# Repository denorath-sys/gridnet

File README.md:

# GRIDNET — Powerline Mesh Terminal

> *Communicate over the power grid. No internet. No GSM. No servers.*

---

## What Is GRIDNET?

GRIDNET is an open hardware mesh communication terminal that uses **existing power line infrastructure** as its transmission medium. Plug the adapter into any wall outlet — the terminal connects to your neighborhood network instantly.

No internet required. No cell towers. No central servers. No accounts.

When grid power fails, the adapter runs from the Terminal's battery over a cable you plug in — the wire is still a conductor whether or not it's energised, so the network keeps working.

The Wi-Fi mesh is not a fallback for the powerline. The two carry to different places: PLC reaches **electrical** neighbours (the same distribution segment, and in practice the same phase), the mesh reaches **physical** ones (adjacent flats, through walls). A neighbour on another phase in the same building is often unreachable over the wire and one mesh hop away. Both run all the time and the router picks per destination — see [`docs/channels.md`](docs/channels.md).

```
Tether:      [Terminal] ←WiFi→ [its own PLC Adapter]      private link to your own modem
PLC:         [Adapter] ←powerline→ [Adapter]              same segment, same phase
Mesh:        [Adapter] ←ESP-NOW→ [Adapter]                physically adjacent, any phase
Outage mode: Grid is down — plug the Terminal into the adapter, network stays alive on battery
```

---

## Why Does This Exist?

Every year, earthquakes, floods, and infrastructure failures cut millions of people off from communication. The internet fails. Cell towers fail. But in most of these scenarios, one thing survives: **the physical power line wiring**.

GRIDNET turns that infrastructure into a resilient local network — inspired by Minitel (France's pre-web national terminal network), FidoNet (a global decentralized BBS built by hobbyists), and the ThinkPad design philosophy (tools built to last).

---

## Hardware Overview

The system consists of two units:

### Terminal
The user-facing device. ThinkPad-inspired clamshell form factor.

| Component | Details |
|---|---|
| **Processor** | GD32VF103CCT6 — RISC-V, 108MHz, 32KB RAM, 256KB Flash |
| **Wireless** | ESP32-C3-MINI-1U — Wi-Fi 2.4GHz mesh + Bluetooth 5.0 LE |
| **Display** | 5.0" TFT LCD, 800×480, RA8875 controller (onboard SDRAM frame buffer), 256 colors, amber-tinted backlight |
| **Keyboard** | 40-key mechanical (Kailh LP), amber LED backlight, red TrackPoint |
| **Right panel** | M1–M4 macro keys + 4×4 numeric keypad + speaker |
| **Speaker** | 1W / 8Ω + PAM8403 amplifier |
| **Storage** | 8MB SPI Flash (LittleFS) + microSD slot |
| **Battery** | 2× 18650, 3350mAh-class genuine cells (~6700mAh total), ~17h active use (screen on) / ~17.5 days standby (screen off, mesh-listen only) — see [`docs/firmware-arch.md`](docs/firmware-arch.md) Power Budget for the full breakdown |
| **Charging** | USB-C, ~4 hours |
| **Antenna** | External, ≤2.33 dBi, on a bulkhead SMA in the case wall — reached by an MHF III / W.FL pigtail from the module's own antenna jack, not by board copper (the module has no RF pad; see [`hardware/pcb/main-board`](hardware/pcb/main-board)) |
| **Dimensions** | 260 × 160 × 28mm, ~680g |
| **OS** | Zephyr RTOS, custom RISC-V BSP |

### PLC Adapter
Separate unit. Plugs directly into any wall outlet (Schuko). Connects to terminal over Wi-Fi — no cables in normal use; during a grid outage the user plugs a USB-C cable in to power it from the Terminal's battery. Replaceable independently.

| Component | Details |
|---|---|
| **PLC SoC** | ST7580 — CENELEC EN50065, OFDM/FSK (band selection under review, see [`docs/electrical-safety.md`](docs/electrical-safety.md)) |
| **Wireless** | ESP32-C3 — Wi-Fi AP for terminal connection |
| **Outage power** | USB-C inlet from the Terminal's battery + 1F supercapacitor hold-up |
| **PLC supply** | MT3608 boost, 5V → 12V for the ST7580's power amplifier |
| **Protection** | TVS P6KE250CA + MOV S20K275 (2 layers; the relay/optocoupler layer went with the inverter) |
| **Power** | HLK-5M05 SMPS, 230VAC → 5VDC |
| **Indicators** | 3× LED: Power / PLC / Wi-Fi |

**Prototype BOM cost: ~$150.22 USD** for one Terminal plus one Adapter — ~$104.35 and ~$45.87 respectively (single unit, retail component pricing). See [`hardware/bom.md`](hardware/bom.md) REV 0.10 for the full breakdown, including why the earlier ~$112 and ~$166.65 figures were both wrong.

---

## Architecture

### Communication Stack

```
┌─────────────────────────────────────────┐
│           APPLICATION LAYER             │
│   Messaging / Games / Forth Apps        │
├─────────────────────────────────────────┤
│           ROUTING LAYER                 │
│   Store-and-forward, 7-day retention    │
│   Mesh routing, automatic repeating     │
├─────────────────────────────────────────┤
│           CHANNEL LAYER                 │
│   Two interfaces, chosen per            │
│   destination by cost — not ranked      │
├─────────────────────────────────────────┤
│           PHYSICAL LAYER                │
│   ST7580 OFDM/FSK, EN 50065-1 limited   │
│   ESP32-C3 Wi-Fi 2.4GHz                 │
└─────────────────────────────────────────┘
```

### Packet Format

```
[AA AA AA][55][LEN 2B][SRC 4B][DST 4B][SEQ 4B][TYPE 1B][PAYLOAD][CRC16 2B]
 preamble  sync  len    source   dest    seq     type     data      checksum

TYPE byte:  [7] SIGNED   [6] RELAYED   [5:0] type code
```

### Addressing

Hierarchical 4-byte address — no central registry required:

```
[CITY 1B][DISTRICT 1B][BUILDING 1B][UNIT 1B]
  01         03           07          12       →  01.03.07.12
```

### Outage Operation

The wire is a conductor whether or not the grid is energising it, so PLC
signalling works during an outage. What stops is the adapter's own power:
it runs from mains, and there is no battery inside it.

So during an outage the adapter runs from the Terminal's battery over a
USB-C cable the user connects. A supercapacitor in the adapter holds it up
long enough to tell the Terminal that mains has gone, so the Terminal can
prompt for the cable. Roughly 5–6 hours of operation with the screen on,
~9 hours with it off.

Nothing is injected onto the wire, and there is no arbitration between
adapters — every node transmits normally under CSMA/CA, exactly as it does
when the grid is up.

Earlier revisions specified a 24V "inverter mode" here instead. It was
removed: it could never have run (the adapter had no power source during
an outage) and it sat 5–24× outside EN 50065-1's signal limits. See
[`docs/plc-adapter-power.md`](docs/plc-adapter-power.md) for the full
analysis, and [`docs/electrical-safety.md`](docs/electrical-safety.md) for
the compliance correction.

### Software Architecture

- **RTOS:** Zephyr (RISC-V support, tickless idle, LittleFS)
- **Boot time:** < 500ms target
- **Tasks:** CHANNEL_MONITOR (0) → PLC_RX (1) → MESH_RX (2) → ROUTER (3) → KEYBOARD (4) → UI (5) → BACKGROUND (6)
- **Filesystem:** LittleFS on 8MB Flash + microSD

Boot screen (Commodore 64 homage):
```
**** GRIDNET OS V1.0 ****
64K RAM SYSTEM  8192K FLASH  BLUETOOTH 5.0
PLC CHANNEL: ACTIVE [3 NODES FOUND]
WIFI BRIDGE: STANDBY  MICROSD: 32GB

READY.
█
```

### Forth VM — Application Platform

Users write and share applications in a sandboxed Forth interpreter (~2KB RAM). Apps are distributed peer-to-peer over the network — like the BBS era.

Security constraints: source address lock, rate limit (5 packets/sec), max 256 bytes/message, filesystem isolation per app.

Example — local market order system in ~15 lines (verified against the
reference VM in [`tools/forth-vm`](tools/forth-vm) — see that directory's
README for why `S"` and `KEY? IF KEY ...` are used instead of the shorter
but non-functional `"` / `KEY? SEND-MSG` you might expect):
```forth
: HEADER
  0 0 S" ╔═══════════════╗" WRITE
  0 1 S" ║  CORNER SHOP  ║" WRITE
  0 2 S" ╚═══════════════╝" WRITE ;

: ORDER
  HEADER
  0 4 S" 1. Bread  2. Milk" WRITE
  KEY? IF KEY S" 01.03.07.99" SEND-MSG THEN ;

: MAIN BEGIN ORDER 1000 WAIT AGAIN ;
MAIN
```

---

## Electrical Safety

GRIDNET puts a low-voltage signal on the mains through a transformer. It does not energise the wire.

- **Signal level is bounded by EN 50065-1**: 5 Vrms at 9 kHz falling to 1 Vrms at 95 kHz. The ST7580's power amplifier delivers 14 V p-p (4.95 Vrms) — ST sized the part to land on that limit — and the adapter adds a hardware current limit as a backstop.
- **PLC signals sit at 95–148.5 kHz**, roughly 2000–3000× the grid frequency. Every household power supply filters that band out; the signal is invisible to their power circuits. Same principle as HomePlug and smart metering, deployed in millions of homes for two decades.
- **Galvanic isolation is mandatory and load-bearing.** The ST7580 reaches the line only through the coupling transformer, and the HLK-5M05 is an isolated supply. The USB-C cable to the Terminal sits on that isolated secondary — the user handles it while the adapter is in a wall socket, so this barrier is what stands between them and the mains.
- **Two protection layers**: TVS (P6KE250CA) for transients, MOV (S20K275) for sustained overvoltage.

⚠️ **One open compliance item**: no EN 50065-1 conformance claim is justified until a conducted-emission sweep is run on a prototype. The band allocation itself is settled — the A-band (9–95 kHz) is reserved for electricity suppliers, so GRIDNET uses B (95–125 kHz) and C (125–140 kHz), and the hardware commits to that choice through Board 1's coupling network ([`docs/plc-coupling.md`](docs/plc-coupling.md), [`docs/protocol.md`](docs/protocol.md)). What remains is the measurement, which needs hardware that does not exist yet. See [`docs/electrical-safety.md`](docs/electrical-safety.md) REV 0.6, which also corrects an earlier claim in this project that a 24V injection was within EN 50065 limits. It was not.

---

## Use Cases

| Scenario | Description |
|---|---|
| 🏚 Disaster response | Coordinate with neighbors when grid, internet, and cell are all down |
| 🏘 Neighborhood messaging | Hyperlocal communication without internet subscriptions |
| 🛒 Local commerce | Shops write their own order systems in Forth — no cloud, no monthly fee |
| 🎮 Games | Turn-based strategy and text adventures played over the power grid |
| 🔒 No cloud | No accounts, no logs, no servers — nothing leaves the neighbourhood. Note that this is *not* the same as confidentiality: the protocol has no encryption yet, and store-and-forward means a message can sit in a relaying neighbour's device for up to 7 days in plaintext. See "Known Gaps" below |
| 👾 Retro / Hacker | Amber display, mechanical keyboard, Forth VM, RISC-V. It boots to READY. |

---

## Project Status

| Component | Status |
|---|---|
| Hardware architecture (dual-board design) | ✅ Complete |
| Communication protocol stack | 🔄 **Under revision — was marked complete, and wasn't.** Three separate design faults are now documented: it does not scale ([`docs/routing.md`](docs/routing.md) — twenty nodes on one segment spend 30.7% of the channel on routing advertisements), it has no authentication of any kind ([`docs/threat-model.md`](docs/threat-model.md)), and its channel model ranks the Wi-Fi mesh as a fallback for the powerline when the two reach different sets of nodes ([`docs/channels.md`](docs/channels.md)). Each has a decided design; none is implemented, and [`docs/protocol.md`](docs/protocol.md) still specifies the old behaviour alongside notices of what replaces it |
| PLC Adapter power architecture ([`docs/plc-adapter-power.md`](docs/plc-adapter-power.md)) | ✅ Complete — adapter runs off the Terminal's battery during an outage; the 24V inverter and its master-election protocol were removed (never able to run, and outside EN 50065-1) |
| Protection circuit (TVS + MOV) | ✅ Complete — two layers, not three: the relay/optocoupler layer went with the inverter. Parts selected ([`hardware/bom.md`](hardware/bom.md)) and now drawn — `P6KE250CA` and `S20K275` are in Board 1's schematic and placed on its PCB |
| Main Board schematic + PCB layout ([`hardware/pcb/main-board`](hardware/pcb/main-board)) | ✅ Complete — custom parts datasheet-verified, PCB placed, routed, ground-poured on both layers, DRC clean (0 violations, 0 unconnected). REV 0.7 was a pre-fab design review that caught a refdes-drift bug placing parts in each other's positions (crystal load caps 51mm from the crystal), a boost-converter switching loop spread across 63mm, and every trace at 0.2mm including a 2.4A path. REV 0.8 found the antenna path was fiction — a phantom U.FL duplicating the module's own jack, a trace nothing could drive, and an invented `ANT` symbol pin — and that the "grid of stitching vias" was nine vias in one column, because `BOX2I.Inflate()` mutates in place (now 167, worst-case return path 55mm → 16.8mm) — see that directory's README |
| PLC/Power Board (BOM's Board 1, the PLC Adapter's PCB — see [`hardware/pcb/plc-board`](hardware/pcb/plc-board)) | ✅ REV 0.3 schematic complete, ERC-clean (350 warnings, 0 errors). Power architecture: Terminal USB-C inlet, Schottky ORing, supercapacitor hold-up, 5V→12V boost feeding the ST7580's `VCC`, hardware transmit-current limit. Line coupling now built too — transmit active filter around the ST7580's own PA, receive resonant filter, and the coupling transformer into the mains. Topology from ST's AN4068, values rescaled from its A-band reference design to GRIDNET's 95–140 kHz band ([`docs/plc-coupling.md`](docs/plc-coupling.md)). PCB placement complete (REV 0.5), now a **four-layer** board: L1/L4 signals, In1.Cu GND plane, In2.Cu +5V plane. Four layers because the ST7580's nine +5V pads on a 48-pin 0.5mm-pitch package need a plane, and two two-layer copper layers are already spoken for by ground and the mains barrier — see that directory's README for the four runs that established it. The 7.96mm isolation barrier cuts all four layers and only the AC-DC module and the coupling transformer cross it; verified geometrically on every pad, track, via and filled zone. **Routed (REV 0.7)**: DRC 0 errors, 0 unconnected, isolation barrier clean on copper. REV 0.6's "one connection short" turned out to be the first gap the repair loop could not close, not the last — the boards behind it had up to nine, all on the ST7580's 0.5mm-pitch QFN. Closing them took a fanout that stopped walling in the signal pins, two parts moved off the QFN's pin field, a 0.15mm escape rule around that one package only (the rest of the board stays 0.2mm), and a repair router that routes through other copper and lifts only what it crosses. The ST7580's grounding was then checked against its datasheet: its VCC capacitor now returns to VSS (Figure 8) rather than through the VSS–GND ferrite, and its exposed pad's thermal vias land on a VSSA island under it. DRC 0 warnings. Still wants a human look at the analog copper around the ST7580 before fab. |
| Case design (CAD) | 📋 Planned — only target external dimensions exist (see Hardware Overview); no CAD model |
| Software architecture (Zephyr + Forth VM) | ⚠️ Complete on paper, with one known conflict — [`docs/threat-model.md`](docs/threat-model.md) found that Ed25519's 1–2KB working set does not fit the `ROUTER` task's 2048B stack, which is why the crypto moves to the ESP32-C3 and the node's identity ends up belonging to that module |
| Electrical safety analysis | ✅ Complete |
| Protocol & Forth VM reference prototypes ([`tools/`](tools/), Python, pre-hardware validation) | ✅ Complete — 90 tests pass. Note that `protocol-sim` implements the protocol as specified today, so the routing, authentication and channel revisions above will need to land there too before they mean anything |
| **PCB fabrication / Hardware prototype** | 🔄 Next step — Main Board has been through two design-review passes and is DRC-clean. RF layout is no longer on its list: there is no RF net on the board (the antenna is a cable assembly from the module's own jack). The stackup is no longer an open decision — it is now `STACKUP` in `build_pcb.py` (1.6mm FR-4, two layers, 1oz copper) and written into the board's own design rules, which turned up that KiCad's manufacturing minimums had been left at zero all along: every "0 violations" this project reported before that had been measured against no process limit at all. The board passes the real rules unchanged. What is left before fab is a return-path review of the SPI/I2C buses and a human eye on the autorouted copper (see [`hardware/pcb/main-board`](hardware/pcb/main-board) "What's not done yet"). Board 1 is placed, four-layer and routed (REV 0.7, DRC-clean). Before it is fabricated it needs a human review of the autorouted analog copper, a part for the ST7580's VSS–GND ferrite (FB1, ≥1.5A), and the mains creepage figure confirmed against the standard; before any EN 50065-1 claim it needs a conducted-emission sweep |
| Embedded firmware (Zephyr, on real hardware) | 📋 Planned — starts after PCB prototype |
| **Link-budget survey** (rides along with the prototype) | 📋 Blocking four documented decisions — cross-phase attenuation, how much of a real segment hears itself, mesh reach through actual walls, and ESP-NOW throughput for small frames. Every routing and channel figure in this project is arithmetic from datasheet-class assumptions, not evidence. This is now the cheapest thing that would tell us whether the design is right |
| Field testing | 📋 Planned |

---

## Known Gaps

Things this design does not currently do. They are listed here rather than
left for a reader to discover, because two of them affect whether the
network can be trusted in the situation it exists for.

**There is no message authentication.** `SRC` is a plaintext field in the
packet header, and on a shared broadcast medium any node can set it to any
value. The sandbox rule in [`docs/protocol.md`](docs/protocol.md) —
"source address locked, app cannot spoof sender" — constrains a Forth app
running on its own device; it says nothing about a modified node. The
consequences follow directly:

- **ROUTE poisoning.** The routing layer is distance-vector with no
  authentication, so any node can advertise `hop_count 0` for an address it
  does not own and pull that traffic to itself.
- **Forged emergency broadcasts.** `BROADCAST 0x03` is flooded to the whole
  mesh and signed by nothing.
- **Storage exhaustion.** Store-and-forward holds messages for 7 days on
  behalf of unauthenticated senders.
- **Unverified code distribution.** `APP_DATA 0x10` moves Forth applications
  peer-to-peer, from peers whose identity is not established.

Firmware updates *are* signed — Ed25519, verified by the bootloader
([`docs/firmware-arch.md`](docs/firmware-arch.md)). The network layer has
no equivalent.

A threat model now exists for closing this: [`docs/threat-model.md`](docs/threat-model.md)
scopes the adversary as a hostile neighbour on the same wire, and records
the decisions — Ed25519 identity bound to an address by trust-on-first-use,
signing tiered so that routing, broadcasts and code are always signed while
ordinary messages are opt-in, and the crypto moved to the ESP32-C3 because
Ed25519's working set does not fit the `ROUTER` task's 2KB stack. **Nothing
is implemented**; the wire format above is still the unauthenticated one.

It is also explicit about what authentication does *not* fix — a signed
route advertisement proves who said it, not that the route exists — and
about what stays out of scope: device theft, traffic analysis and jamming.

**`ROUTE` does not scale, independently of security.** Twenty nodes on one
distribution segment would spend 30.7% of a 2.4 kbps channel on routing
advertisements alone. [`docs/routing.md`](docs/routing.md) redesigns it
around a property the original missed — a PLC segment is a broadcast domain,
so one-hop neighbours can be learned passively at zero airtime cost — which
takes the same case to 1.89%. That document also states, for the first time
in this project, what topology the network is assumed to have, and flags
that the assumption has never been measured.

**Duplicate addresses are not detected.** Addresses are self-assigned with
no registry, and `docs/protocol.md` currently attributes collision
detection to CSMA/CA. That is a media-access mechanism — it detects a busy
channel, not two nodes claiming `01.03.07.12`. Nothing in the protocol
notices the duplicate, and the routing table oscillates when it happens.

**No encryption.** Message contents are plaintext on the wire and plaintext
in every relaying device's store-and-forward queue.

---

## Repository Structure

```
gridnet/
├── README.md
├── LICENSE                    (CERN-OHL-W-2.0)
├── CONTRIBUTING.md
├── hardware/
│   ├── pcb/
│   │   ├── main-board/         (Board 2 — KiCad schematic + routed, ground-poured PCB, see its README)
│   │   └── plc-board/          (Board 1 — KiCad schematic + routed PCB, see its README)
│   └── bom.md                 (bill of materials)
├── docs/
│   ├── protocol.md            (full protocol stack)
│   ├── firmware-arch.md       (Zephyr + Forth VM)
│   ├── threat-model.md        (adversary scope, attacks, auth decisions)
│   ├── routing.md             (why ROUTE doesn't scale, and the redesign)
│   ├── channels.md            (PLC vs mesh: what each actually reaches)
│   ├── electrical-safety.md   (CENELEC compliance)
│   ├── plc-adapter-power.md   (adapter power architecture + EN 50065 analysis)
│   └── plc-coupling.md        (line coupling network: AN4068 retuned for B+C)
├── firmware/
│   └── README.md              (planned structure — embedded firmware not started)
├── tools/
│   ├── protocol-sim/          (Python reference implementation of docs/protocol.md)
│   └── forth-vm/              (Python prototype of the sandboxed Forth VM)
└── media/
    ├── logo-cyan.svg
    └── logo-silver.svg
```

Note: `hardware/case/` and `hardware/schematics/` (now just a pointer to
`hardware/pcb/`) aren't in the tree above because there's nothing under
either yet worth listing — see the Project Status table above.

---

## Looking For

- Hardware engineer with embedded systems / PCB experience
- Anyone with real-world ST7580 / PLC field experience
- Zephyr RTOS developers (RISC-V BSP, driver development)
- Forth enthusiasts — help design the VM standard library
- Beta testers willing to run a node in their building

Open an Issue or email directly if you're interested in collaborating.

---

## Inspiration

**Minitel** — France's pre-web national terminal network. A whole country connected, locally, before the internet existed.

**FidoNet** — A global decentralized BBS network built by hobbyists. Store-and-forward over phone lines. No servers. No company.

**ThinkPad** — A design philosophy: every detail intentional, built to last, keyboard first.

---

## License

Hardware designs and documentation: [CERN Open Hardware Licence v2 — Weakly Reciprocal (CERN-OHL-W-2.0)](https://ohwr.org/cern_ohl_w_v2.txt)

Firmware (when released): GPL-3.0

© 2026 Yasar — Open Hardware Project

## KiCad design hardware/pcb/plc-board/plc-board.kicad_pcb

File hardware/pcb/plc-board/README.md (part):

GRIDNET — PLC/Power Board KiCad Schematic + PCB
REV 0.7 (Board 1, the PLC Adapter's own PCB — see "Board 1 is the PLC
Adapter's PCB" below.)

What changed in REV 0.7
------------------------

**The board is routed.** `route.sh` now runs from placement to a finished
board: 753 track segments and 173 vias over F.Cu and B.Cu, both planes
poured, DRC **0 errors, 0 warnings, 0 unconnected**, and
`check_isolation_barrier()` clean on copper.

**U4's grounding now follows the ST7580 datasheet** (DocID022644 Rev 2), read
for this pass rather than assumed:

- **C11 decouples VCC to VSS, not GND.** Figure 8 draws VCC's capacitor to
  VSS, and "all supply voltages must be properly filtered to their respective
  ground". C11 went to GND, which put the PA's supply loop — up to 1 A,
  I(PA_OUT)MAX — through FB1, the ferrite Figure 9 puts between VSS and GND.
  Every other supply capacitor already matched Figure 8.
- **The exposed pad's thermal vias land on copper.** Table 2: the pad is
  "electrically connected to VSSA" and should be "thermally connected to a
  copper ground plane"; Table 5's 50 °C/W is "mounted on a 2-side + vias PCB
  with a ground dissipating area on the bottom side". The plane under it is
  GND, so its sixteen vias were cut out of it and DRC called them dangling.
  The pour step now adds a VSSA island under the pad, inside U4's pin ring,
  on In1.Cu (37 mm²) and B.Cu (28 mm², less where escape routes cross).
- **Tying the pad to GND directly would have been wrong.** Figure 9 joins the
  exposed pad, VSSA and VSS, and reaches GND only through a ferrite bead —
  which is what the schematic already did.
- **FB1 carries the PA's DC return** (the 12V boost is GND-referenced), so
  `hardware/bom.md` now asks for ≥1.5 A and low DC resistance.

Also: `route.sh` bounds Freerouting with `FREEROUTING_TIMEOUT` (300 s) and
treats a run that writes no session as a failed attempt. The same DSN that
finished in 17 s on one run sat for ten minutes on the next, and the import
of nothing used to hand all 172 nets to the repair router.

REV 0.6 reported every run ending "one connection short". That was wrong, and
the reason it was wrong is the first thing this pass found:

**`finish_routing.py` stopped at the first pair it could not repair.** So
"one short" was the first hard gap, not the last — the board behind one such
report still had nine. The loop now sets a hard pair aside, works the rest,
retries set-aside pairs whenever the gap count falls below its best so far,
and lists every remaining gap when it gives up. Counting progress as "fewer
gaps than ever" rather than "a repair reported success" matters: one run
"finished" the same `/ST_VDD_A` gap six times with copper that never closed
it.

Once the real list was visible, every remaining gap was on **U4, the ST7580**
— a 48-pin 0.5mm-pitch QFN with its power pins interleaved among signals —
and the causes were in this toolchain and this placement, not in luck:

- **The repair rip-up looked at the wrong end.** It searched for neighbours to
  move around the pair's *second* end; on every REV 0.6 run the stranded end
  was the first (U4 pins 39 and 41).
- **The power fanout walled in the signals.** One via per power pad, in line,
  1.6mm out: each blocked both neighbouring rows, and on U4's right edge
  (48 47 +5V, 46 VDD_B, 45 GND, 44 43 42 +5V, 41 40 39 signals) every signal
  had one across its only way out. Adjacent same-net pads now share one
  bridged via from the run's middle; spacing is checked by real distance,
  stubs included; +5V goes before GND (GND has the F.Cu pour to fall back on);
  a pad boxed in on both sides can dogleg into an unused neighbour's row (U4
  pin 33, between two +5V stubs, lands its via beside NC pin 32); and a pad
  left without a fanout is reported. It used to skip three of U4's thirteen
  silently; pin 45 then came back from routing joined to nothing but a 1.8mm²
  sliver of pour.
- **R6 and C15 sat on top of U4's pin field.** R6 was 0.4mm above pins 3–8,
  leaving 1.35mm for two fanout vias and the five JTAG signals plus RESETN on
  their way to J3. C15 sat across pins 9–12, far from the Rx tank it belongs
  to (RX_IN is pin 19, on the *left* edge). R6 moved up and left of the pins;
  C15 moved beside R20 and L2.
- **0.2mm track and 0.2mm clearance cannot get U4's signals out.** Pins 4 and
  5 sit between pin 3's +5V via and pin 6's GND via, whose copper is 0.9mm
  apart; two tracks need 1.0mm. Adjacent pins cannot fan out at 45° either
  (0.354mm between them, 0.4mm needed). So there is now a **fine-pitch escape
  rule, around U4 only**: a named rule area `U4_ESCAPE` (courtyard + 3mm) and
  a custom rule in `plc-board.kicad_dru` drop clearance to 0.15mm inside it,
  and U4's signal nets form an `Escape` netclass routed at 0.15mm. Everything
  else stays at 0.2/0.2, which DRC was checked to still enforce outside the
  area. `PA_OUT` and `VSSA` stay at Default width — they carry the PA's
  current. The process minimum in `STACKUP` drops to 0.15mm so the rule is
  legal; JLCPCB's standard four-layer process goes to 0.09mm.

And the repair router learned to finish:

- **Route through, lift only what is crossed.** Re-routing every neighbour
  from scratch as a pad chain kept failing on the one neighbour that could not
  get back in. `lift_route()` instead runs A* with other nets' unlocked copper
  passable at a cost, then lifts exactly the segments the result comes within
  clearance of; the cut ends are repaired as ordinary gaps. Neighbours with
  more than six pads (`/ST_VSSA`) are cut locally rather than re-routed.
- **Orphan pads.** A planed pad on its own pour island with no via is found
  and stitched — from the pad if it can escape, else anywhere inside the
  island, lifting the one or two segments in the chosen spot's way.
- **Locked copper.** Every via and stub `build_pcb.py` places is locked, and
  repair never touches locked copper. Before this, ripping up `/ST_VSSA` as a
  neighbour removed U4's sixteen thermal vias, which nothing would have put
  back. The locks survive the Freerouting round trip.
- **The board edge.** Freerouting does not keep KiCad's 0.5mm copper-to-edge
  rule (it laid `/ST_RESETN` 0.26mm from the top edge), so offending
  autorouter copper is removed and re-routed. The repair router's own margin
  now includes the copper's half-width and is measured from the Edge.Cuts
  geometry; `GetBoardEdgesBoundingBox()` includes the outline's line width and
  sat 0.075mm outside the real edge, and on the right and bottom the margin was
  counted from the end of a grid 1mm larger than the board.
- **Zones are refilled after every repair**, since the pour now comes before
  repair, and **a cleanup pass** deletes what repair leaves behind (dangling
  stubs, duplicate vias, Freerouting's via 0.05mm off a locked fanout via),
  driven by DRC's own UUIDs, then re-checks that nothing came apart.
- **Each repair step runs in a fresh Python process.** Once copper has been
  taken off a board, KiCad 9's SWIG layer hands back any later board's objects
  as bare `SwigPyObject`s and segfaults on exit. `route.sh` can also keep each
  failed attempt's board (`KEEP_FAILED=dir`); the next attempt's placement
  used to overwrite it.

Two more corrections: `route.sh` drops the escape area from the DSN (KiCad's
Specctra exporter writes every rule area as a keepout, which would have fenced
Freerouting out of exactly that region), and rule areas are now honoured by
what they forbid rather than by being rule areas at all.

The routed board came from the first attempt of the run that produced it, but
attempts differ — Freerouting is not deterministic — and earlier runs with
only some of these changes needed several. This was produced with KiCad 9.0.3
and Freerouting 2.2.4 on Java 25; KiCad 9.0.3 reproduces the REV 0.6 placement
exactly (same parts, nets, vias and zones), and reports 475 ERC warnings, 0
errors, on the REV 0.6 schematic where REV 0.6 quoted 350 — a version
difference, the same count either side of a regeneration. With C11 moved to
VSS it reports 473 warnings, 0 errors.

What changed in REV 0.6
------------------------

**The stackup is a rule now, not a sentence.** `STACKUP` in `build_pcb.py`
is written into the board's design settings: 1.6mm FR-4, four layers, 1oz
outer copper (0.5oz inner, which does not matter here — the inner layers carry
only planes and every current-carrying trace, the 1.0mm mains nets included,
is on an outer layer), 0.2mm minimum track and clearance, 0.6mm vias on 0.3mm
drills, 0.15mm annular ring, 0.25mm hole-to-hole.

This came out of closing the same item on the Main Board, where it exposed
something worse than an undocumented assumption: KiCad's minimums default to
zero, and both boards carried `m_TrackMinWidth = 0.0` and
`m_MinClearance = 0.0` through every DRC run this project has reported. A
0.05mm trace would have passed.

It caught something here immediately. The power fanout sends each of U4's
power pads 1.6mm straight out, and those pads are on a 0.5mm pitch — so their
vias landed on a 0.5mm pitch too, which with a 0.3mm drill is 0.2mm
hole-to-hole against the 0.25mm rule. Three pairs. The fanout now checks
hole spacing and steps a crowded neighbour further out.

A routing pass. It did not finish — every run still ends one connection
short — but what it found is worth more than the routing would have been:
six separate defects stood between this board and a routed one, and each was
invisible until the router hit it.

**The QFN's power pins had no fanout.** The ST7580 puts nine +5V pads on
three edges of a 48-pin 0.5mm-pitch package. Nothing passes between adjacent
pads there, so each escapes radially, and the router then has to bring nine
radial escapes back together around the outside of eleven others. Every run
this project had made died on that. `add_power_fanout()` now gives each power
pad a 1.6mm stub and a via at build time — what a person does by hand on a
QFN and what no autorouter does for itself.

**The pour ran after the repair, so the fanout vias were islands.** Planes
are what connect those vias; until the copper is poured they are isolated
points, and the repair router was being asked to tie them together — the
exact problem the fanout removes. `route.sh` now pours before repairing. This
is not the ordering the Main Board warns about: there the danger is pouring
before *routing*, which makes the autorouter treat GND as done. With those
two changes together, +5V stopped being a holdout at all.

**The repair router ignored netclasses.** It laid 0.2mm track at 0.2mm
clearance into the `Mains` class, which is 1.0mm at 2.5mm — on the mains side
that is not a style question, it is the live-to-neutral spacing. Seven
clearance errors in one run, every one on `/AC_L`, `/AC_N` or `/PLC_LINE`,
all laid by the step meant to be finishing the job. It now reads the rules
from the same table `build_pcb.py` writes into the project file: KiCad 9's
Python binding returns `GetNetClass()` as a bare object with no accessors, so
importing the source of truth is both simpler and harder to get out of step.

**Correcting that exposed a floorplan that could not satisfy it.** Four mains
nets at 1.0mm and 2.5mm need a 3.5mm pitch — about 16.5mm of channel with
margins — and the mains column had 9.7mm once the parts were in it. The
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
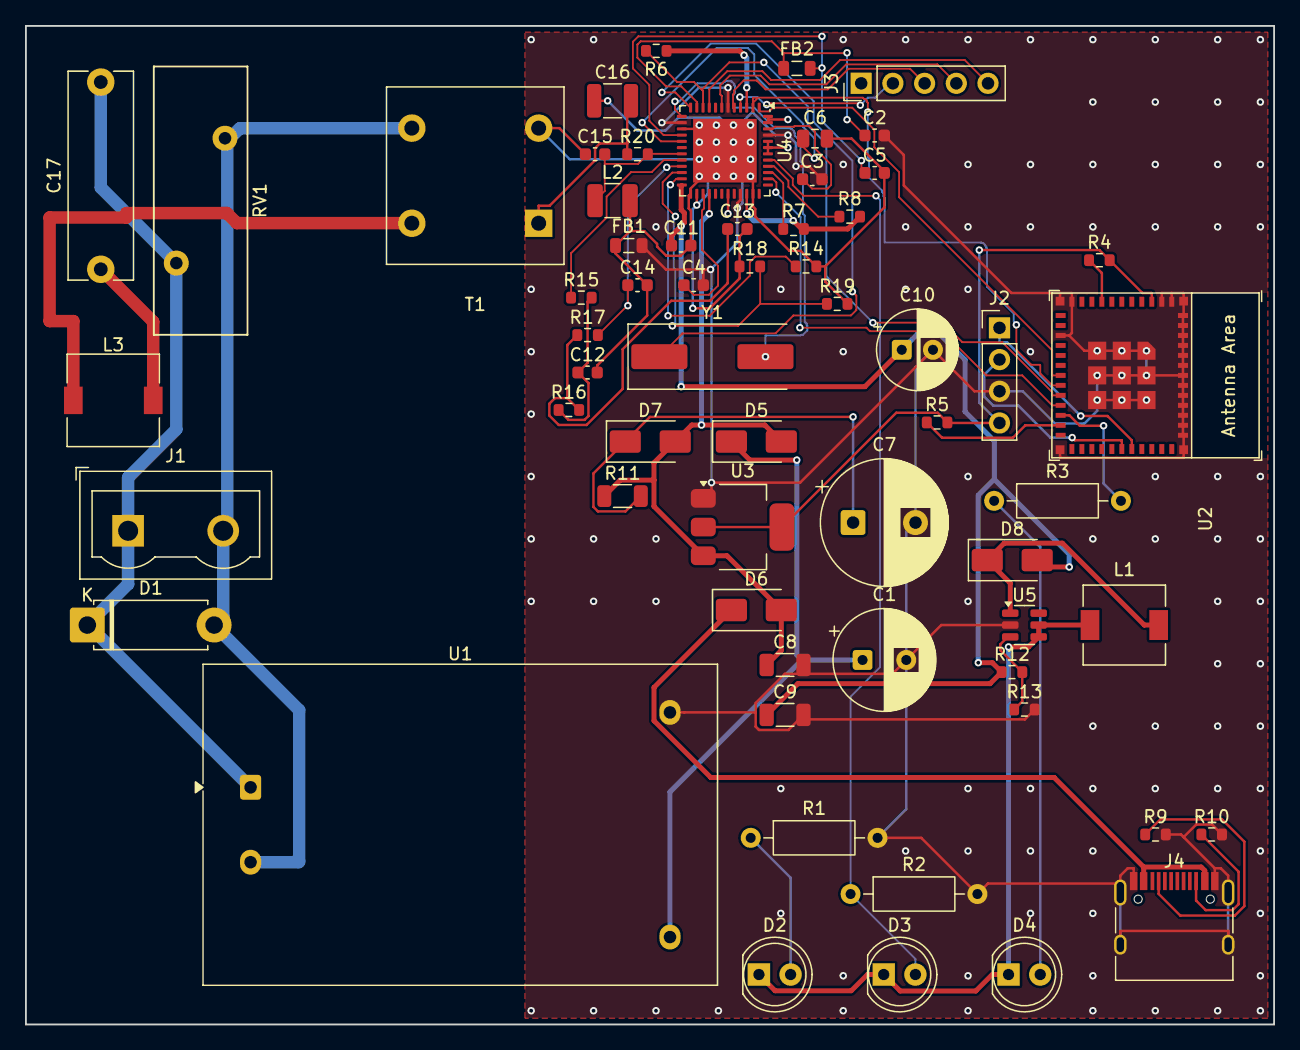
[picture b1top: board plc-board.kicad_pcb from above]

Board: 4 copper layers, 100.0 x 80.0 mm, 62 parts (0 on the bottom side), 50 nets.

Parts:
C1: 220uF; CP_Radial_D8.0mm_P3.50mm
C2, C3, C4, C5, C11: 100nF; C_0603_1608Metric
C6: 1uF; C_0805_2012Metric
C7: 1F 5.5V; CP_Radial_D10.0mm_P5.00mm
C8, C9: 22uF; C_1206_3216Metric
C10: 100uF; CP_Radial_D6.3mm_P2.50mm
C12: 1nF C0G; C_0603_1608Metric
C13, C14: 68pF C0G; C_0603_1608Metric
C15: 12nF; C_0603_1608Metric
C16: 10uF/50V X5R; C_1210_3225Metric
C17: 150nF X1; C_Rect_L16.5mm_W5.0mm_P15.00mm_MKT
D1: P6KE250CA; D_5W_P10.16mm_Horizontal
D2: LED (green); LED_D5.0mm
D3: LED (amber); LED_D5.0mm
D4: LED (blue); LED_D5.0mm
D5, D6, D7, D8: SS34; D_SMA
FB1, FB2: FB; L_0805_2012Metric
J1: MAINS_L_N; TerminalBlock_Wuerth_691311400102_P7.62mm
J2: ESP32_UART0_PROGRAMMING; PinHeader_1x04_P2.54mm_Vertical
J3: ST7580_JTAG_DEBUG; PinHeader_1x05_P2.54mm_Vertical
J4: TERMINAL_5V_IN; USB_C_Receptacle_HRO_TYPE-C-31-M-12
L1: 22uH; L_6.3x6.3_H3
L2: 150uH; L_1210_3225Metric
L3: 12uH; L_7.3x7.3_H4.5
R1, R2: 1k; R_Axial_DIN0207_L6.3mm_D2.5mm_P10.16mm_Horizontal
R3: 330R; R_Axial_DIN0207_L6.3mm_D2.5mm_P10.16mm_Horizontal
R4, R5, R6, R7, R8, R19: 10k; R_0603_1608Metric
R9, R10, R16: 5.1k; R_0603_1608Metric
R11: 10R; R_1206_3216Metric
R12: 19.1k; R_0603_1608Metric
R13, R15: 1k; R_0603_1608Metric
R14: 270R; R_0603_1608Metric
R17: 22k; R_0603_1608Metric
R18: 33k; R_0603_1608Metric
R20: 150R; R_0603_1608Metric
RV1: S20K275; RV_Disc_D21.5mm_W7.5mm_P10mm
T1: 750510231; Transformer_Wuerth_750510231
U1: HLK-5M05; Converter_ACDC_Hi-Link_HLK-5Mxx
U2: ESP32-C3-MINI-1
U3: AMS1117-3.3; SOT-223-3_TabPin2
U4: ST7580; QFN-48-1EP_7x7mm_P0.5mm_EP5.1x5.1mm
U5: MT3608; SOT-23-6
Y1: 8MHz; Crystal_SMD_HC49-SD

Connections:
+5V: C8.1, D2.1, D3.1, D4.1, D5.2, D6.2, D7.2, J3.1, L1.1, R6.2, R7.2, R8.2, R11.1, U3.3, U4.3, U4.28, U4.31, U4.34, U4.42, U4.43, U4.44, U4.47, U4.48, U5.4, U5.5
/+3V3: J2.4, R4.2, R5.2, U2.3, U3.2
/+12V: C9.1, C10.1, C11.1, D8.2, R12.1, U4.24
/AC_L: C17.2, D1.1, J1.1, RV1.1, U1.1
/AC_N: D1.2, J1.2, RV1.2, T1.7, U1.2
/BOOST_FB: R12.2, R13.1, U5.3
/BOOST_SW: D8.1, L1.2, U5.1
/ESP_EN: R4.1, U2.8
/ESP_IO9: R5.1, U2.23
/ESP_U0RXD: J2.2, U2.30
/ESP_U0TXD: J2.1, U2.31
/PLC_COUPLING: C16.2, R20.1, T1.1
/PLC_LED: D3.2, R2.1, U4.41
/PLC_LINE: L3.1, T1.10
/PLC_LINE_X1: C17.1, L3.2
/PSU_5V: C1.1, D5.1, U1.4
/PWR_LED_R: D2.2, R1.1
/ST_BR0: R8.1, U4.40
/ST_BR1: R7.1, U4.39
/ST_CL: R14.1, U4.23
/ST_PA_IN_N: R18.2, R19.1, U4.22
/ST_PA_IN_P: C14.1, R17.2, U4.21
/ST_PA_OUT: C13.2, C16.1, R18.1, U4.26
/ST_PA_SK: C13.1, R16.2, R17.1
/ST_RESETN: R6.1, U2.20, U4.10
/ST_RXD: U2.19, U4.2
/ST_RX_IN: C15.1, L2.1, R20.2, U4.19
/ST_TCK: J3.4, U4.7
/ST_TDI: J3.5, U4.9
/ST_TMS: J3.3, U4.5
/ST_TRSTN: J3.2, U4.4
/ST_TXD: U2.18, U4.1
/ST_TX_FILT: C12.1, R15.2, R16.1
/ST_TX_OUT: R15.1, U4.20
/ST_T_REQ: U2.21, U4.38
/ST_VCCA: C6.1, U4.17
/ST_VDD_A: C2.1, FB2.1, U4.11
/ST_VDD_B: C3.1, U4.46
/ST_VDD_PLL: C5.1, FB2.2, U4.16
/ST_VDD_REG_1V8: C4.1, U4.27
/ST_VSSA: C5.2, C6.2, C11.2, C12.2, C14.2, C15.2, FB1.1, L2.2, R14.2, R19.2, T1.4, U4.15, U4.25, U4.35, U4.49
/ST_XIN: U4.12, Y1.1
/ST_XOUT: U4.13, Y1.2
/SUPERCAP: C7.1, D7.1, R11.2
/USB_5V: D6.1, J4.A4, J4.A9, J4.B4, J4.B9
/USB_CC1: J4.A5, R9.1
/USB_CC2: J4.B5, R10.1
/WIFI_LED_CTRL: D4.2, R3.1
/WIFI_LED_GPIO: R3.2, U2.22
GND: C1.2, C2.2, C3.2, C4.2, C7.2, C8.2, C9.2, C10.2, FB1.2, J2.3, J4.A1, J4.A12, J4.B1, J4.B12, J4.S1, R1.2, R2.2, R9.2, R10.2, R13.2, U1.3, U2.1, U2.2, U2.11, U2.14, U2.36, U2.37, U2.38, U2.39, U2.40, U2.41, U2.42, U2.43, U2.44, U2.45, U2.46, U2.47, U2.48, U2.49, U2.50, U2.51, U2.52, U2.53, U3.1, U4.6, U4.14, U4.33, U4.45, U5.2

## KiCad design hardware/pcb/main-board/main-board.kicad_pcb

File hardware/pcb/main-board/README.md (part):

GRIDNET — Main Board KiCad Schematic
REV 0.8 (matches hardware/bom.md's Board 2 — Main Board bill of materials)

What this is
------------

A KiCad 9 schematic (`main-board.kicad_sch`) for the Main Board, covering
the full circuit from hardware/bom.md's "Board 2" line items: USB-C power
input, Li-ion charge/boost/regulation, the GD32VF103CCT6 MCU with clock/
reset/boot/SWD, SPI flash + SRAM + microSD + RTC, the ESP32-C3-MINI-1U
wireless module, and the off-board connectors for the display, keyboard
controller, keyboard backlight, and speaker. There is no antenna path on
this board and no RF net — see "The antenna path never touched the board".

Alongside it, `main-board.kicad_pcb` has every part placed within the
100x80mm board outline from hardware/bom.md, **fully routed** on 2
layers (F.Cu/B.Cu) with sized power traces, and **poured with ground on
both layers**. `kicad-cli pcb drc` comes back completely clean: 0
violations of any severity, 0 unconnected items.

REV 0.8 continues the pre-fab review with two findings that the REV 0.7
pass created the conditions to see, both about things the board *claimed*
to have and did not:

1. **The antenna path never touched the board.** A phantom U.FL connector
   (`J7`) duplicating one the module already carries, a fictional `/ANT_RF`
   trace to the SMA, and an invented `ANT` symbol pin behind both. All
   three are gone, and with them the RF layout gap that headed "What's not
   done yet". See "The antenna path never touched the board".
2. **The "grid of stitching vias" was one column of nine**, because
   `BOX2I.Inflate()` mutates in place. The pours were tied together only
   down the left edge: the worst-case point on the board was 55mm from the
   nearest GND via. Now 16.8mm. See "The stitching grid was one column of
   nine vias".

REV 0.7 was the pre-fabrication design-review pass over the routed board.
Four things came out of it, in rough order of how badly they would have
bitten:

1. A **reference-designator drift bug** that had silently moved a dozen
   components into each other's board positions — including the 8MHz
   crystal's load capacitors, which ended up 51mm and 34mm away from the
   crystal. See "Reference-designator drift" below.
2. The **IP5306's switching loop spread across the whole board** — the
   boost inductor sat 63mm from the IC. See "The IP5306 switching loop".
3. **Every trace on the board was 0.2mm**, including the boost path
   rated for 2.4A. See "Trace widths".
4. **No ground plane** — every ground connection was an ordinary routed
   trace. See "Ground pours".

A fifth finding is about the tooling rather than the board: Freerouting
reports success while silently dropping connections, so the flow now
verifies with DRC and repairs what is missing. See "Routing".

An earlier revision also regenerated this PCB after it had been routed
against a *wrong* netlist: the datasheet verification pass described
below fixed real pin-numbering bugs in three of the four custom parts,
which changed which schematic pin number carries which signal for the
MCU, the ESP32-C3 module, and the IP5306, so the old copper was not just
stale but actually wrong (see "Datasheet verification results").

Neither file is hand-drawn in the KiCad GUI: both are generated by the
Python scripts in `kicad_gen/` — the schematic places components at grid
coordinates and wires them via net-label stubs (the standard label-based
wiring pattern for busy schematics, rather than long point-to-point wires
across the sheet); the PCB script places real footprints using each
part's actual courtyard geometry (measured via `pcbnew`, not guessed) so
placement is collision-free from the start. `kicad_gen/route.sh` drives
the whole sequence end to end; see "Regenerating / validating" below.

The antenna path never touched the board
-----------------------------------------

"What's not done yet" used to open with RF layout: `/ANT_RF` ran from `U9`
to a U.FL pad (`J7`) and on to the edge-mount SMA (`J8`) at whatever width
Freerouting chose, and wanted a coplanar-waveguide geometry computed for
this stackup. Working out that geometry was the plan for this pass. The
first thing that turns up on opening the board is that **`/ANT_RF` has no
`U9` pad on it at all** — the net is two connectors wired to each other,
and nothing drives it.

The ESP32-C3-MINI-1U does not bring its radio out to a castellated pad.
Datasheet v2.2 Table 3-1 lists all 53 pads: pins 1, 2, 11, 14 and 36–53
are GND, and the rest are `3V3`, `EN` and IO. There is no ANT and no RF
pad anywhere in the list. The radio leaves the module through the antenna
jack **mounted on the module itself** — that is what the "U" in `-1U`
means. So:

- `kicad_gen/build_library.py`'s symbol had a pin whose *number* was the
  string `"ANT"`, matching no pad in the footprint. That is why the
  netlist quietly produced a two-connector net instead of an error: KiCad
  ties schematic pins to footprint pads by pin number, and a pin number
  that matches nothing simply contributes nothing.
- `J7` was a second, board-mounted U.FL duplicating the module's own. The
  schematic comment beside it said as much — "U.FL pad on the
  ESP32-C3-MINI-1U module itself" — but it was placed on the PCB as a real
  footprint at (80, 35.53) anyway.
- The trace from `J7` to `J8` was therefore 19mm of copper (three
  segments, 0.2mm wide) between two connectors and nothing else, which is
  what an RF review would have been asked to impedance-match.

Worse, an edge-mount SMA soldered to the board cannot be reached by a
pigtail in the first place: its centre pin *is* a board pad. hardware/bom.md
line items 13 and 14 described exactly that — an SMA connector plus a
"U.FL-to-SMA pigtail" to connect the module to it — which cannot be
assembled as written.

**And the pigtail was the wrong connector generation.** Datasheet section
10.2 specifies the module's jack as the *third generation* connector,
compatible with Hirose **W.FL**, I-PEX **MHF III** and Amphenol **AMC**,
with a body of 2.05 x 1.7 x 1.40mm (Figure 10-3). U.FL / MHF I is the
first generation and about 2.6mm across. A U.FL plug does not mate with it.
Every mention of "U.FL" in this project's Board 2 documentation was wrong
about the part on the module, independently of everything above.

What the board looks like now: `J7` and `J8` are gone from the schematic,
from `PLACEMENT` in `build_pcb.py` and from the PCB; the `ANT` pin is gone
from the symbol; `/ANT_RF` is gone as a net. The antenna is a cable
assembly and a case feature, not copper — an MHF III/W.FL plug-to-SMA-jack
pigtail from the module's own connector to a bulkhead SMA in the enclosure
wall, with the antenna screwing onto that. hardware/bom.md REV 0.6 carries
all three as Board 2 items 13–15, with the connector and pigtail marked as
enclosure/cable parts rather than parts that get placed on this PCB — and
with the antenna itself, which REV 0.5 never listed at all.

This removes the largest item from "What's not done yet" rather than
solving it: there is no controlled-impedance net on this board, no antenna
keepout to observe (datasheet Figure 3-1 Note A: the keepout zone applies
to the PCB-antenna `-1` variant, "the latter has no antenna keepout zone"),
and no RF corridor for via placement to respect. The antenna requirements
move to the cable and the case: 2.4GHz, 50Ω, and **maximum gain 2.33 dBi**,
which is the gain of the antenna Espressif certified the module with —
exceed it and the module's existing test reports no longer cover the
product (datasheet section 10.2).

The stitching grid was one column of nine vias
------------------------------------------------

"Ground pours" below describes a 5mm grid of stitching vias placed
"wherever one fits clear of every courtyard, pad and trace". Counting them
on the finished board: **nine, all at x = 1.1mm, running down the left edge
from y = 1.1 to y = 41.1**, then stopping. Nothing else on the board.

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
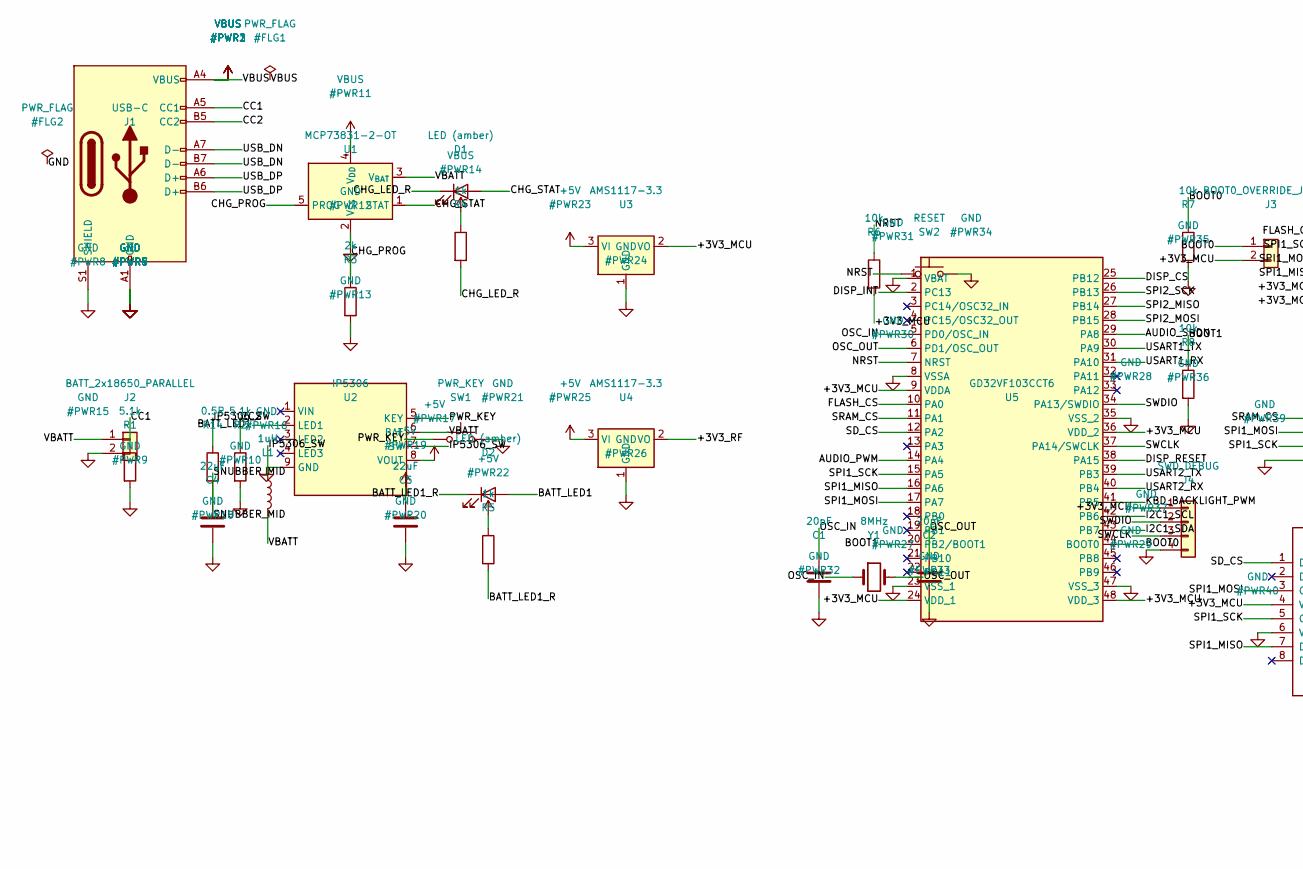
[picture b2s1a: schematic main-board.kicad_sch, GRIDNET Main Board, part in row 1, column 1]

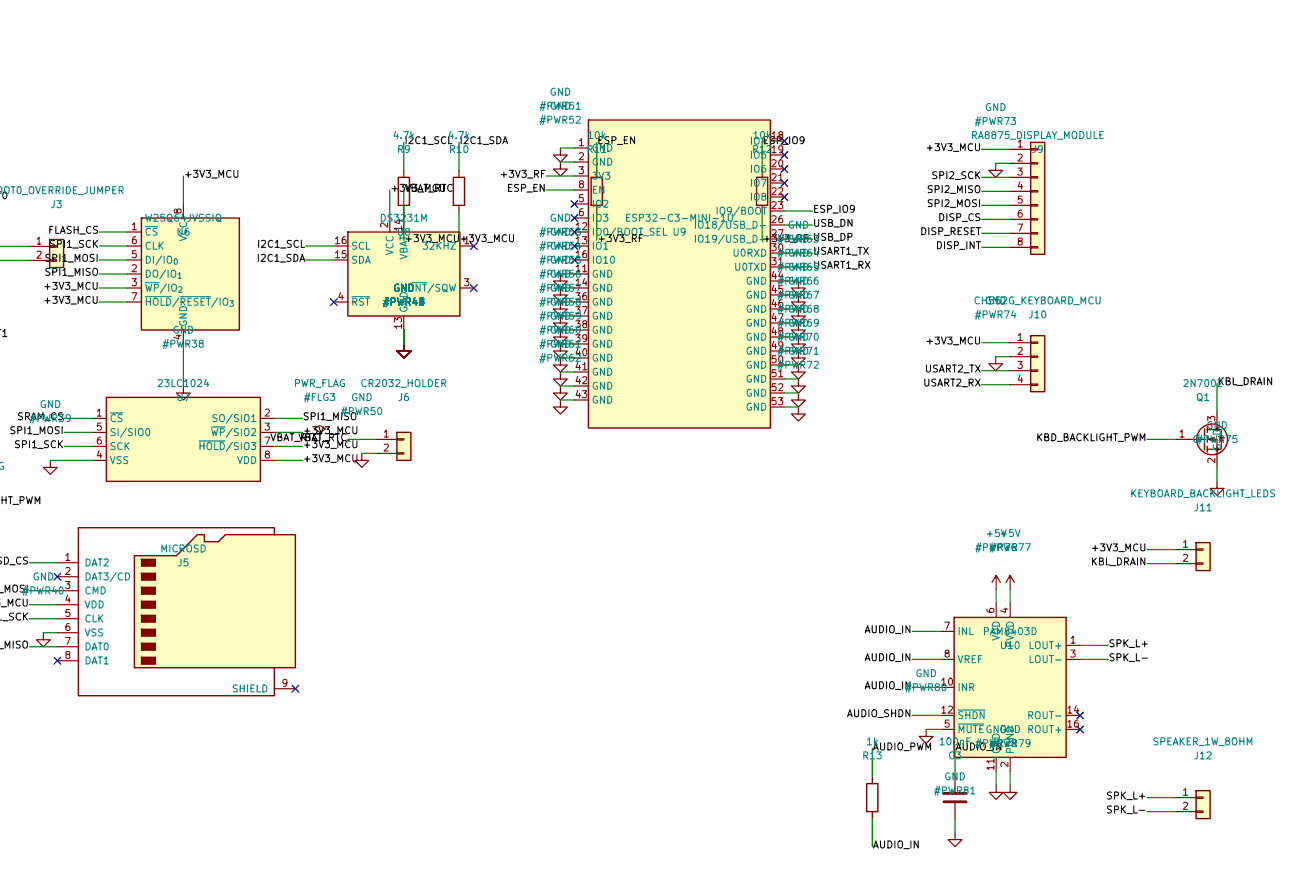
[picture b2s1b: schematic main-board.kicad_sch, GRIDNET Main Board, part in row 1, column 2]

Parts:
C1, C2: 20pF; C_0603_1608Metric
C3: 100nF; C_0603_1608Metric
C4, C5: 22uF; C_0805_2012Metric
D1, D2: LED (amber); LED_0603_1608Metric
J1: USB-C; USB_C_Receptacle_HRO_TYPE-C-31-M-12
J2: BATT_2x18650_PARALLEL; JST_PH_B2B-PH-K_1x02_P2.00mm_Vertical
J3: BOOT0_OVERRIDE_JUMPER; PinHeader_1x02_P2.54mm_Vertical
J4: SWD_DEBUG; PinHeader_1x04_P2.54mm_Vertical
J5: MICROSD; microSD_HC_Molex_104031-0811
J6: CR2032_HOLDER; BatteryHolder_MYOUNG_BS-07-A1BJ001_CR2032
J9: RA8875_DISPLAY_MODULE; PinHeader_1x08_P2.54mm_Vertical
J10: CH552G_KEYBOARD_MCU; PinHeader_1x04_P2.54mm_Vertical
J11: KEYBOARD_BACKLIGHT_LEDS; PinHeader_1x02_P2.54mm_Vertical
J12: SPEAKER_1W_8OHM; PinHeader_1x02_P2.54mm_Vertical
L1: 1uH; L_6.3x6.3_H3
Q1: 2N7002; SOT-23
R1, R2: 5.1k; R_0603_1608Metric
R3: 2k; R_0603_1608Metric
R4, R5, R13: 1k; R_0603_1608Metric
R6, R7, R8, R11, R12: 10k; R_0603_1608Metric
R9, R10: 4.7k; R_0603_1608Metric
R14: 0.5R; R_0603_1608Metric
SW1: PWR_KEY; SW_PUSH_6mm_H4.3mm
SW2: RESET; SW_PUSH_6mm_H4.3mm
U1: MCP73831-2-OT; SOT-23-5
U2: IP5306; SOP-8_3.9x4.9mm_P1.27mm
U3, U4: AMS1117-3.3; SOT-223-3_TabPin2
U5: GD32VF103CCT6; LQFP-48_7x7mm_P0.5mm
U6: W25Q64JVSSIQ; SOIC-8_5.3x5.3mm_P1.27mm
U7: 23LC1024; SOIC-8_3.9x4.9mm_P1.27mm
U8: DS3231M; SOIC-16W_7.5x10.3mm_P1.27mm
U9: ESP32-C3-MINI-1U
U10: PAM8403D; SOP-16_3.9x9.9mm_P1.27mm
Y1: 8MHz; Crystal_SMD_HC49-SD

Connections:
+5V: C5.1, R5.1, U2.8 (VOUT), U3.3 (VI), U4.3 (VI), U10.4 (PVDD), U10.6 (VDD), U10.13 (PVDD)
/+3V3_MCU: J3.2, J4.1, J5.4 (VDD), J9.1, J10.1, J11.1, R6.2, R9.2, R10.2, U3.2 (VO), U5.9 (VDDA), U5.24 (VDD_1), U5.36 (VDD_2), U5.48 (VDD_3), U6.3 (~WP/IO_{2}), U6.7 (~HOLD/~RESET/IO_{3}), U6.8 (VCC), U7.3 (~WP/SIO2), U7.7 (~HOLD/SIO3), U7.8 (VDD), U8.2 (VCC)
/+3V3_RF: R11.2, R12.2, U4.2 (VO), U9.3 (3V3)
/AUDIO_IN: C3.1, R13.2, U10.7 (INL), U10.8 (VREF), U10.10 (INR)
/AUDIO_PWM: R13.1, U5.14 (PA4)
/AUDIO_SHDN: U5.29 (PA8), U10.12 (~SHDN)
/BATT_LED1: D2.2 (A), U2.2 (LED1)
/BATT_LED1_R: D2.1 (K), R5.2
/BOOT0: J3.1, R7.1, U5.44 (BOOT0)
/BOOT1: R8.1, U5.20 (PB2/BOOT1)
/CC1: J1.A5 (CC1), R1.1
/CC2: J1.B5 (CC2), R2.1
/CHG_LED_R: D1.1 (K), R4.2
/CHG_PROG: R3.1, U1.5 (PROG)
/CHG_STAT: D1.2 (A), U1.1 (STAT)
/DISP_CS: J9.6, U5.25 (PB12)
/DISP_INT: J9.8, U5.2 (PC13)
/DISP_RESET: J9.7, U5.38 (PA15)
/ESP_EN: R11.1, U9.8 (EN)
/ESP_IO9: R12.1, U9.23 (IO9/BOOT)
/FLASH_CS: U5.10 (PA0), U6.1 (~CS)
/I2C1_SCL: R9.1, U5.42 (PB6), U8.16 (SCL)
/I2C1_SDA: R10.1, U5.43 (PB7), U8.15 (SDA)
/IP5306_SW: L1.1, R14.1, U2.7 (SW)
/KBD_BACKLIGHT_PWM: Q1.1 (G), U5.41 (PB5)
/KBL_DRAIN: J11.2, Q1.3 (D)
/NRST: R6.1, SW2.1, U5.7 (NRST)
/OSC_IN: C1.1, U5.5 (PD0/OSC_IN), Y1.1
/OSC_OUT: C2.1, U5.6 (PD1/OSC_OUT), Y1.2
/PWR_KEY: SW1.1, U2.5 (KEY)
/SD_CS: J5.1 (DAT2), U5.12 (PA2)
/SNUBBER_MID: C4.1, R14.2
/SPI1_MISO: J5.7 (DAT0), U5.16 (PA6), U6.2 (DO/IO_{1}), U7.2 (SO/SIO1)
/SPI1_MOSI: J5.3 (CMD), U5.17 (PA7), U6.5 (DI/IO_{0}), U7.5 (SI/SIO0)
/SPI1_SCK: J5.5 (CLK), U5.15 (PA5), U6.6 (CLK), U7.6 (SCK)
/SPI2_MISO: J9.4, U5.27 (PB14)
/SPI2_MOSI: J9.5, U5.28 (PB15)
/SPI2_SCK: J9.3, U5.26 (PB13)
/SPK_L+: J12.1, U10.1 (LOUT+)
/SPK_L-: J12.2, U10.3 (LOUT-)
/SRAM_CS: U5.11 (PA1), U7.1 (~CS)
/SWCLK: J4.3, U5.37 (PA14/SWCLK)
/SWDIO: J4.2, U5.34 (PA13/SWDIO)
/USART1_RX: U5.31 (PA10), U9.31 (U0TXD)
/USART1_TX: U5.30 (PA9), U9.30 (U0RXD)
/USART2_RX: J10.4, U5.40 (PB4)
/USART2_TX: J10.3, U5.39 (PB3)
/USB_DN: J1.A7 (D-), J1.B7 (D-), U9.26 (IO18/USB_D-)
/USB_DP: J1.A6 (D+), J1.B6 (D+), U9.27 (IO19/USB_D+)
/VBATT: J2.1, L1.2, U1.3 (V_{BAT}), U2.6 (BAT)
/VBAT_RTC: J6.1, U8.14 (VBAT)
GND: C1.2, C2.2, C3.2, C4.2, C5.2, J1.A1 (GND), J1.A12 (GND), J1.B1 (GND), J1.B12 (GND), J1.S1 (SHIELD), J2.2, J4.4, J5.6 (VSS), J6.2, J9.2, J10.2, Q1.2 (S), R1.2, R2.2, R3.2, R7.2, R8.2, SW1.2, SW2.2, U1.2 (V_{SS}), U2.9 (GND), U3.1 (GND), U4.1 (GND), U5.1 (VBAT), U5.8 (VSSA), U5.23 (VSS_1), U5.35 (VSS_2), U5.47 (VSS_3), U6.4 (GND), U7.4 (VSS), U8.5 (GND), U8.6 (GND), U8.7 (GND), U8.8 (GND), U8.9 (GND), U8.10 (GND), U8.11 (GND), U8.12 (GND), U8.13 (GND), U9.1 (GND), U9.2 (GND), U9.11 (GND), U9.14 (GND), U9.36 (GND), U9.37 (GND), U9.38 (GND), U9.39 (GND), U9.40 (GND), U9.41 (GND), U9.42 (GND), U9.43 (GND), U9.44 (GND), U9.45 (GND), U9.46 (GND), U9.47 (GND), U9.48 (GND), U9.49 (GND), U9.50 (GND), U9.51 (GND), U9.52 (GND), U9.53 (GND), U10.2 (PGND), U10.5 (~MUTE), U10.11 (GND), U10.15 (PGND)
VBUS: J1.A4 (VBUS), J1.A9 (VBUS), J1.B4 (VBUS), J1.B9 (VBUS), R4.1, U1.4 (V_{DD})

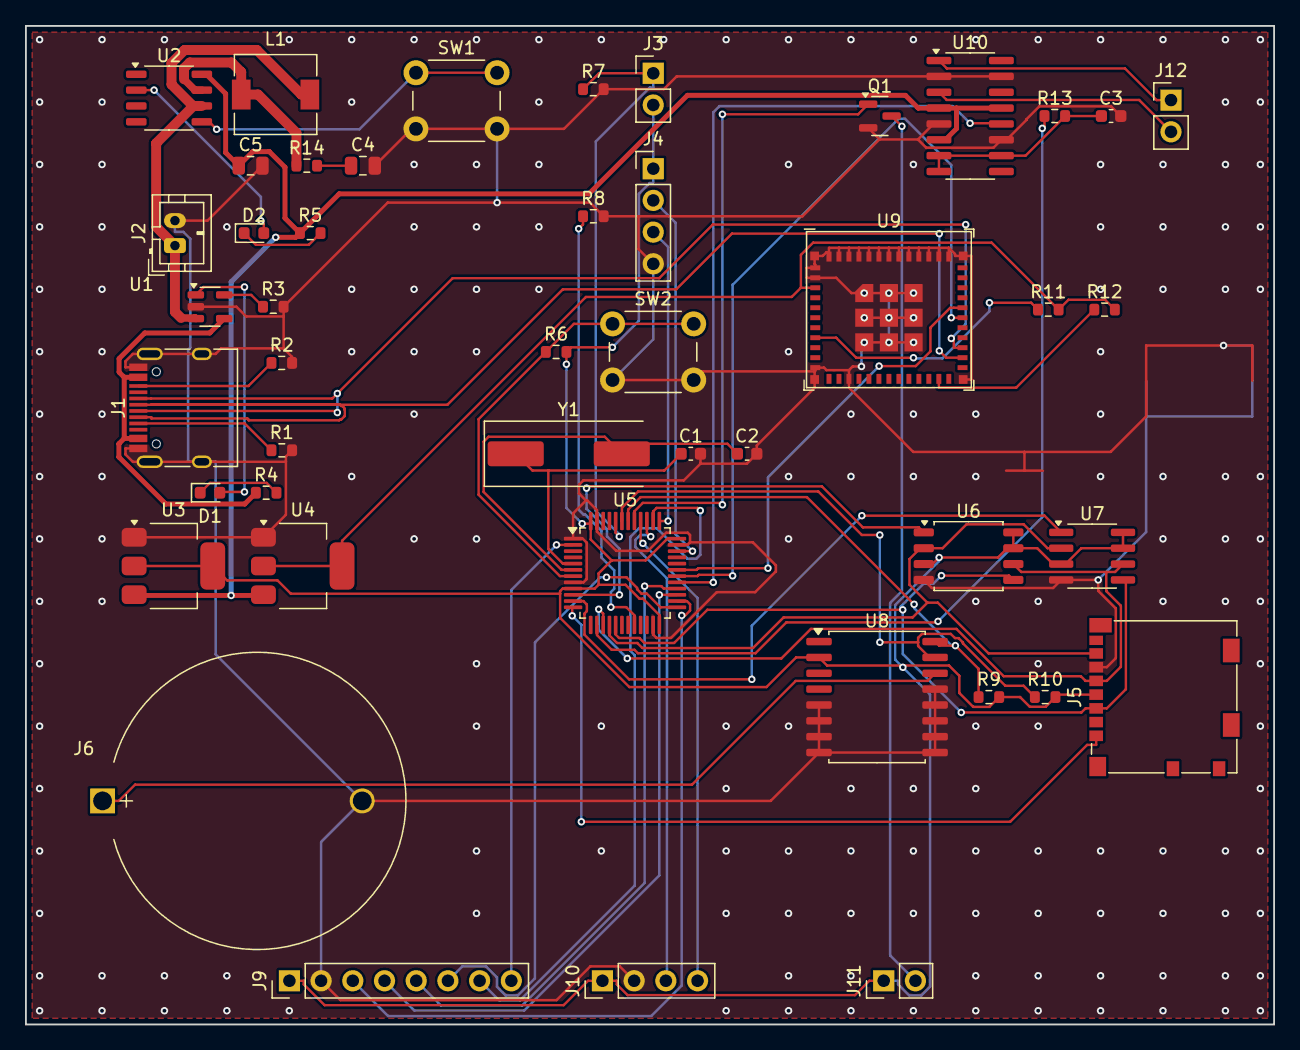
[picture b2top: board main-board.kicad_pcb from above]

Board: 2 copper layers, 100.0 x 80.0 mm, 46 parts (0 on the bottom side), 53 nets.

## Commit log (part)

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2026-04-09 README.md
2026-04-09 LICENSE
2026-04-09 bom.md
2026-04-09 protocol.md
2026-04-09 firmware-arch.md
2026-04-09 electrical-safety.md
2026-04-09 inverter-master.md
2026-04-09 logo-cyan.svg
2026-04-09 logo-silver.svg
2026-04-10 CONTRIBUTING.md

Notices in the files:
hardware/pcb/main-board/README.md:
(CC-BY-SA 4.0, the same license terms as KiCad's own official libraries),
hardware/pcb/plc-board/README.md:
`gridnet_footprints.pretty/` (CC-BY-SA 4.0), same source and process as
